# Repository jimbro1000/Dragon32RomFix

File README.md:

# Dragon 32 Rom Adapter Fix #

This project details a simple conversion board to replace
two 8K masked ROMs with a single modern EEPROM.

The board is designed to accept 28 pin eeproms compatible with the
Atmel AT28C range.

## Direct (Twin) Rom Replacement ##

If the replacement ROM is a AT28C64 the board must be configured
for a 1:1 swap with one adapter for each ROM position. There is no
need to fit any of the SMT components or the 3 pin jumper.

If the replacement ROM is a AT28C256 the board needs to be 
assembled with the 3 pin jumper and a resistor at R1 and R3. The
jumper at JP2 must be bridged. This then allows the selection of a 
different ROM image by moving the JP1 jumper between positions 
(only when powered down). Only half of the ROM capacity will be 
used and the images should be loaded at $0000 and $4000. The
memory space between $2000-$3FFF and $6000-$7FFF cannot be
accessed in this mode without modifying the board.

### Bodging the Board ###

In order to fully utilise the available memory space in this
configuration it is necessary to find a way to drive pin 26 of
the eeprom by optionally inverting the signal to it.

The NAND gate position at U2 can be used as an inverter by taking 
the signal from pin 20 of the input socket and feeding it to J1. 
Some cutting of traces will also be needed to avoid
Putting a jumper or switch on that lead will allow you to 
switch between the two possible memory spaces (effectively 
giving you 4 selectable images). Ideally it should be a jumper 
with the "off" position going to pin 3 of JP1 (the pin furthest 
from R1).

## Single Rom Setup ##

If the replacement ROM is a AT28C256 the board can be configured 
for a 2:1 swap. In this arrangement it is essential to fully
populate the board with all 3 resistors and the NAND gate. A fly
lead from J1 is also needed.

In this arrangement the board should be fitted to position IC18
with the flylead going to pin 20 of IC17.

JP1 still allows swapping between two different ROM images but
all of the memory space on the ROM will be utilised. The first
image is from $0000-$3FFF and the second image is from $4000-$7FFF.

It is possible to fit the board in position IC17 but the ROM images
will need resequencing:

$0000-$1FFF => ROM1 1-1  
$2000-$3FFF => ROM1 1-0  
$4000-$5FFF => ROM2 1-1  
$6000-$7FFF => ROM2 1-0  

# BOM #

| Position | Component |
| -------- | --------- |
| R1, R2, R3 | 4K7 0805 |
| U1 | 2 x 12 position 2.54mm pin header | 
| U2 | 74AHCT1G00 SOT-353 | 
| U3 | DIP-28 socket | 
| JP1 | 3-pin right-angle 2.54mm pin header |

The resistor values given are recommended - all 3 are acting as 
pull-up or pull-down purposes so smaller or larger values can be
used as appropriate. It is also possible to simply solder bridge 
the positions but this has potential to damage the EEPROM.

For the U1 pin headers I recommend using turned-pins *and* fitting 
a turned-pin socket on the main board to ensure a quality fit and 
no damage from repeated insertions. Using square pins will 
ultimately damage a regular single- or double-wipe socket but it
is possible to fit female pin headers to ensure compatibility but
this then prevents putting regular (original) Dragon ROMs back in.

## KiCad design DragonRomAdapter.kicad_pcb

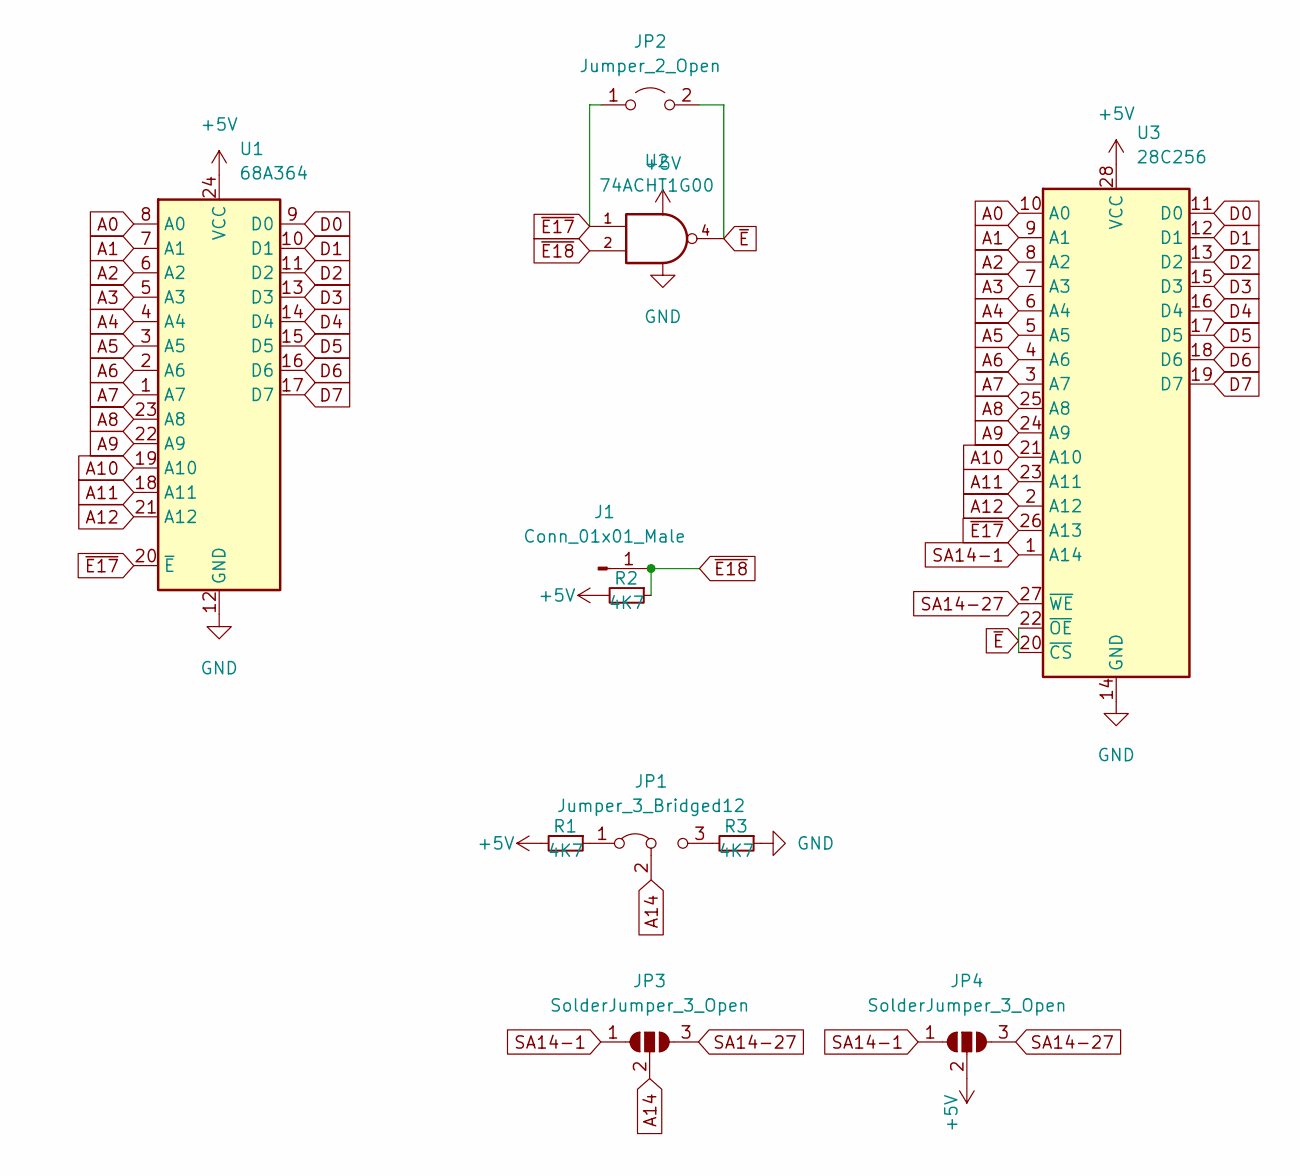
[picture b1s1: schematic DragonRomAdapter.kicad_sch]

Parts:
J1: Conn_01x01_Male; PinHeader_1x01_P2.54mm_Vertical
JP1: Jumper_3_Bridged12; PinHeader_1x03_P2.54mm_Horizontal
JP2: Jumper_2_Open; SolderJumper-2_P1.3mm_Open_TrianglePad1.0x1.5mm
JP3, JP4: SolderJumper_3_Open; SolderJumper-3_P1.3mm_Open_RoundedPad1.0x1.5mm_NumberLabels
R1, R2, R3: 4K7; R_0805_2012Metric_Pad1.20x1.40mm_HandSolder
U1: 68A364; DIP-24_W15.24mm
U2: 74ACHT1G00; SOT-353_SC-70-5_Handsoldering
U3: 28C256; DIP-28_W15.24mm

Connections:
+5V: JP4.2 (C), R1.2, R2.2, U1.24 (VCC), U2.5 (VCC), U3.28 (VCC)
A0: U1.8 (A0), U3.10 (A0)
A1: U1.7 (A1), U3.9 (A1)
A2: U1.6 (A2), U3.8 (A2)
A3: U1.5 (A3), U3.7 (A3)
A4: U1.4 (A4), U3.6 (A4)
A5: U1.3 (A5), U3.5 (A5)
A6: U1.2 (A6), U3.4 (A6)
A7: U1.1 (A7), U3.3 (A7)
A8: U1.23 (A8), U3.25 (A8)
A9: U1.22 (A9), U3.24 (A9)
A10: U1.19 (A10), U3.21 (A10)
A11: U1.18 (A11), U3.23 (A11)
A12: U1.21 (A12), U3.2 (A12)
A14: JP1.2 (C), JP3.2 (C)
D0: U1.9 (D0), U3.11 (D0)
D1: U1.10 (D1), U3.12 (D1)
D2: U1.11 (D2), U3.13 (D2)
D3: U1.13 (D3), U3.15 (D3)
D4: U1.14 (D4), U3.16 (D4)
D5: U1.15 (D5), U3.17 (D5)
D6: U1.16 (D6), U3.18 (D6)
D7: U1.17 (D7), U3.19 (D7)
GND: R3.1, U1.12 (GND), U2.3 (GND), U3.14 (GND)
unnamed: JP1.1 (A), R1.1
unnamed: JP1.3 (B), R3.2
SA14-1: JP3.1 (A), JP4.1 (A), U3.1 (A14)
SA14-27: JP3.3 (B), JP4.3 (B), U3.27 (~WE)
~E17: JP2.1 (A), U1.20 (~E), U2.1, U3.26 (A13)
~E18: J1.1, R2.1, U2.2
~E: JP2.2 (B), U2.4, U3.20 (~CS), U3.22 (~OE)

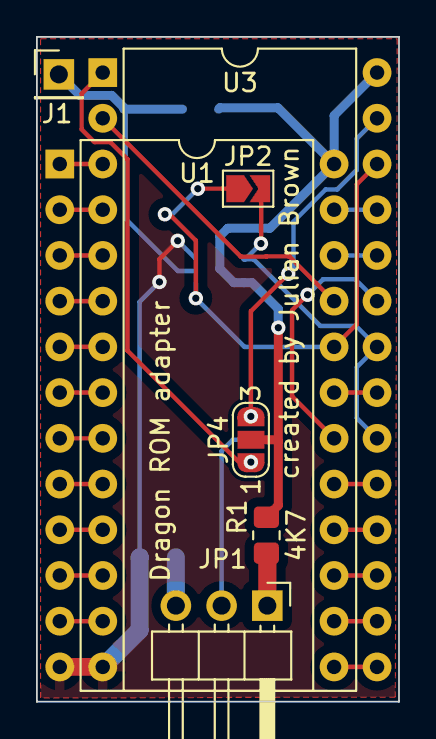
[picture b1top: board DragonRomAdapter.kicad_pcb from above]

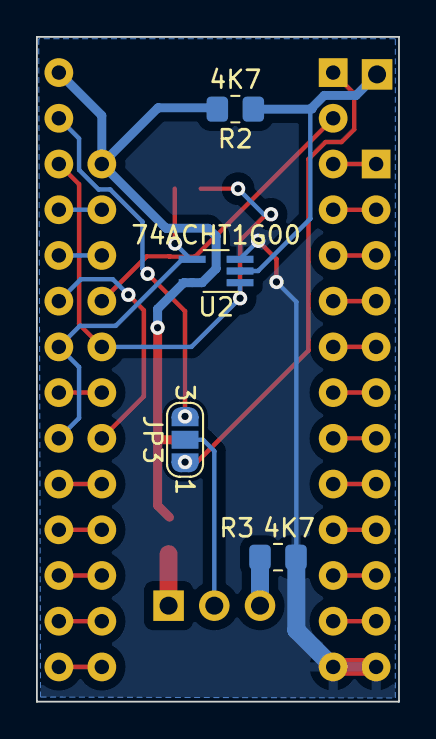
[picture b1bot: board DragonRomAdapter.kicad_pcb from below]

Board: 2 copper layers, 20.1 x 36.9 mm, 11 parts (4 on the bottom side), 31 nets.

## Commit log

2022-11-23 tidy-up board
2022-11-27 reduce size of board to fit some main boards
2023-02-22 use acht logic instead of LVC
2023-02-22 migrate to kicad 7
2023-09-11 make adapter compatible with 28c and 27c roms
